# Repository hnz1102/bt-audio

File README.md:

# bt-audio

A Bluetooth A2DP sink for the original ESP32, written in Rust. It receives
audio from a phone or PC over Bluetooth Classic and plays it through two
TAS5754M class-D amplifiers (main L/R and woofer) fed over I2S. The volume of
each amplifier is set with a potentiometer.

The diagram also shows the planned FPGA DSP stage (crossover and filters)
between the ESP32 and the amplifiers. Until it exists, the ESP32 is wired
straight to both amplifiers.

## How it works

```
Bluetooth (A2DP/SBC) -> Bluedroid decoder -> bounded channel -> I2S writer thread -> 2x TAS5754M
                                                       volume knobs (ADC) -> I2C ---^
```

- The ESP32 advertises itself as `ESP32-Speaker` and accepts pairing
  automatically (SSP numeric comparison, with a legacy PIN of `1234` as
  fallback).
- Several devices can be paired; Bluedroid keeps the bonds in NVS. A new
  device can pair only while the speaker is discoverable: 3 min after
  "Pairing mode" in the web UI, and always while no device is paired (being
  discoverable takes radio time from the audio stream). Paired devices can connect whenever no other device is
  connected.
- At boot the speaker connects to the paired device that connected last; if
  that one is not reachable it tries the next most recent, and so on (up to
  8 devices). The order and the device names are kept in NVS (`src/bt.rs`).
- The Bluedroid stack decodes SBC and hands 16-bit stereo PCM to a callback
  running on the Bluetooth task. The callback copies each packet into a
  jitter buffer (at most 32 KB, ~185 ms) and drops it if the buffer is full
  or the free heap would fall below 12 KB, so a slow I2S write never stalls
  the Bluetooth stack. The drops are logged every minute by reason (buffer
  full / heap short, with the lowest free heap at a heap-short drop).
- Playback starts once 80 ms of audio is buffered, and buffers again after
  the stream paused long enough to run dry. Some sources (Windows PCs) pause
  and then send a burst; the buffer rides that out. The I2S DMA holds another
  ~43 ms. The `i2s-writer` thread runs on CPU1 at priority 15, away from the
  Bluetooth and WiFi tasks on CPU0. The buffer keeps 16-bit PCM, half the memory of the 32-bit DMA
  slots. The minute log reports underruns and rebuffers during playback, and
  after a drop or underrun also the buffer level, its peak and the free heap.
- A separate `i2s-writer` thread applies a software gain, then writes to the
  I2S channel.
- The I2S sample rate follows the rate negotiated by the source (16, 32,
  44.1 or 48 kHz).
- The I2S master outputs MCLK, BCK and WS. The APLL is the clock source, so
  the clocks are exact and low-jitter; if it cannot produce a rate the driver
  falls back to the 160 MHz PLL and logs a warning. MCLK is set to 256 x fs,
  but the original ESP32 puts the I2S module clock on GPIO0, so the pin
  carries 512 x fs (22.58 MHz at 44.1 kHz), which the TAS5754M accepts. GPIO0
  runs at the strongest drive, because the BOOT switch and the auto-reset
  transistor on it round a weaker edge into a triangle.
- The 2.1ch crossover runs on the ESP32: 4th-order Linkwitz-Riley, 150 Hz by
  default, set with `crossover_hz` (50-300 Hz) in the web UI. L/R are high-passed for the main
  amplifier; the mono sum (L+R)/2 is low-passed for the woofer. The woofer path also has
  a subsonic high-pass (4th order, 30 Hz by default) against cone buzz, set
  with `subsonic_hz` in the web UI (applies at once, 0 = off), and a bass EQ
  (peaking boost, Q 0.9; `bass_eq_hz` 30-150 Hz, default 60 Hz, `bass_eq_db`
  0-12 dB, default +6 dB) to make up for the small woofer's low-end roll-off.
  Keep the subsonic filter on when boosting.
- Both TAS5754M share one data line. I2S runs with 32-bit slots (BCK = 64 x fs);
  each slot holds the 16-bit main sample in its upper half and the 16-bit
  woofer sample in its lower half. Over I2C both amplifiers are set to I2S
  16-bit input; the woofer amplifier also gets an I2S shift of 16 SCLKs
  (P0-R41) so it reads the lower half. Both woofer channels carry the same
  mono signal. Their own DSP stays at its default.
- A peak limiter on each path (main L/R linked, woofer) turns loud peaks down
  instead of hard-clipping them; low-passing the mono sum can push bass peaks
  past full scale. How often it engaged is logged every 60 s.
- Volume ceiling from PVDD: the amplifiers' SPK_GAIN/FREQ divider (150 kΩ /
  750 kΩ, about 5.8 V) selects the 26 dBV gain, at which digital full scale
  would need a ~30 V output peak. The firmware measures PVDD through the
  AP33772S every 5 s and limits the volume register so full scale stays
  within 90 % of PVDD (about -4.5 dB at 20 V, -16.5 dB at 5 V). Change
  `AMP_GAIN_DBV` if the divider changes.
- If the woofer amplifier does not answer at boot, the crossover is off and the
  main amplifier plays the full range.
- After Bluetooth and the audio path are up, a `net` thread joins the WiFi
  network (see [WiFi, web UI and syslog](#wifi-web-ui-and-syslog)); the audio
  path never waits on it.
- At start-up, before the I2S and the amplifiers, the firmware talks to the
  AP33772S USB PD sink controller on the same I2C bus (address `0x52`): it
  reads the source's PDOs, enables the UVP/OVP/OCP protections, requests the
  highest voltage the source offers up to the `pd_max_mv` setting (24 V by default; a fixed
  PDO counts at its own voltage, a PPS/AVS PDO up to its maximum) and switches
  VOUT on once the negotiation succeeds. A PPS / AVS contract needs no
  keep-alive from the firmware: the AP33772S repeats the request itself. At boot the firmware waits up to
  5 s for the source to start USB PD; a failed negotiation is retried every
  minute. After start-up only the `controls` thread talks to the AP33772S. If no voltage is available or the
  request fails, VOUT stays off and an error is logged. The sequence follows the wrapper in
  `uv-controller`.
- An amplifier that does not answer on I2C at boot is treated as not fitted:
  it is left alone until the next reboot and the other one runs on its own
  (the web UI shows it as "not connected"). The I2C driver is installed from a
  task pinned to CPU1, so its interrupt runs away from the Bluetooth
  controller and WiFi on CPU0; on CPU0 it had tripped the interrupt watchdog.
- A `controls` thread reads the two knobs every 20 ms (ADC spikes dropped,
  smoothed, with hysteresis so a knob left alone never moves the volume). The
  volume is applied digitally on the ESP32, ramped sample by sample and
  dithered to 16 bits, so turning a knob does not click; the amplifier volume
  registers stay at the PVDD ceiling and are only used to mute. The main
  knob is the master volume for both amplifiers (0 dB down to -60 dB; fully
  counter-clockwise mutes both). The
  bass knob sets the woofer level against it: the lower half goes from -12 dB
  below the master up to the master level at mid rotation (fully
  counter-clockwise mutes the woofer); the upper half goes from the master
  level up to the woofer's full output at the top, whatever the master is, so
  the woofer can play at full with the main speakers quiet. Full output is the
  PVDD ceiling plus up to +6 dB of digital boost, with the woofer limiter
  holding the peaks. A muted knob unmutes only once it is clearly past the
  mute point, so noise near the bottom of the rotation cannot switch the
  sound on and off. The thread also watches `SPK_FAULT` and clears a latched
  fault by toggling `SPK_MUTE`.
- `SPK_MUTE` is low (muted) at boot and whenever no stream is running, and
  high while audio plays. The amplifiers ramp the volume, so there are no pops.

### The TAS5754M amplifier: closed loop and BTL

Japanese version: [docs/tas5754m_closed_loop_btl_ja.png](docs/tas5754m_closed_loop_btl_ja.png)

- **Closed loop.** Inside the TAS5754M the I2S data goes through the DSP
  (interpolation filter, digital volume) to a DAC, which produces the voltage
  the output should have. The PWM output of the H bridge is fed back (before
  the external LC filter) and compared with it; a loop filter integrates the
  difference and corrects the PWM duty cycle. The loop cancels PVDD ripple and
  changes (high PSRR) and the distortion of the output stage (MOSFET
  resistance, dead time).
- **Gain.** The gain is set by the feedback ratio only, selected with the
  `SPK_GAIN/FREQ` pin. This board's 150 kΩ / 750 kΩ divider selects
  26.4 dBV, at which digital full scale asks for about a 29.7 V output peak.
  The output cannot swing past about 90 % of PVDD (about 18 V at 20 V), so the
  firmware caps the volume from the measured PVDD (-4.5 dB at 20 V).
- **BTL (bridge-tied load).** Each channel has two half bridges, `OUT+` and
  `OUT-`, driving the two speaker terminals in opposite phase. The voltage
  across the speaker swings ±PVDD: twice the voltage and four times the
  power of a single-ended output, with no DC on the speaker and so no
  coupling capacitor. Neither speaker terminal may be connected to GND.
- **1SPW modulation.** In the TAS5754M mostly one side switches at a time
  (`OUT+` on positive half-waves, `OUT-` on negative ones) and at idle both
  sides only make narrow pulses, so the idle current is low; the TAS5756M's
  BD modulation has slightly lower distortion instead. The waveforms in the
  diagram are simplified.

The Rust side lives in [src/main.rs](src/main.rs). A small C component,
[components/bt_shim](components/bt_shim), wraps the Bluetooth controller
start-up, the I2S driver, the I2C bus and the ADC, whose configuration macros
and structs are awkward to use from Rust.

## Hardware

- An original ESP32 (classic Bluetooth is not available on the S2, S3, C3 and
  later chips).
- Two TAS5754M amplifiers wired as in Figure 83 of the datasheet (2.2 dual
  stereo BTL schematic, [tas5754m.pdf](tas5754m.pdf)): U400 drives the main
  L/R speakers, U401 the woofer. Supplies: PVDD 5-24 V for the amplifiers and
  3.3 V for the logic, shared with the ESP32.
- An AP33772S USB PD sink controller board on the I2C bus (SDA/SCL below,
  address `0x52`); its VOUT is the PVDD supply, which the TAS5754M allows up
  to 26.4 V.
- Two 10 kΩ B-taper (linear) potentiometers for the main and woofer volume.
  The firmware maps the rotation to the volume in dB evenly. For A-taper
  (audio) pots set `POT_TAPER_MID` to 0.15 (15 % at half rotation) and the
  firmware undoes the A curve; the default 0.5 is for a linear B pot.
- 16 MB flash (the partition table and `sdkconfig.defaults` assume it; adjust
  `CONFIG_ESPTOOLPY_FLASHSIZE_*` for other sizes).

### Wiring

| Signal | ESP32 GPIO | TAS5754M pin (both amplifiers) |
|--------|-----------|-------------------------------|
| BCK | 26 | SCLK (23) |
| WS / LRCK | 25 | LRCK/FS (25) |
| DATA (DOUT) | 22 | SDIN (24) |
| MCLK | 0 | MCLK (22) |
| SDA | 21 | SDA (16), 4.7 kΩ pull-up to 3.3 V |
| SCL | 18 | SCL (17), 4.7 kΩ pull-up to 3.3 V |
| Mute | 13 | SPK_MUTE (27), 100 kΩ pull-down to GND |
| Fault | 34 | SPK_FAULT (40), 10 kΩ pull-up to 3.3 V |
| Main volume | 33 (ADC1) | wiper of the main potentiometer |
| Woofer volume | 35 (ADC1) | wiper of the woofer potentiometer |

The pins are constants at the top of [src/main.rs](src/main.rs). Details:

- **I2C bus:** it runs at 100 kHz (the speed used by `uv-controller` for the
  AP33772S). The AP33772S (`0x52`) and the amplifiers (`0x4C`, `0x4D`) share it.
- **I2C addresses:** strap `ADR0`/`ADR1` so that U400 (main) is `0x4C`
  (`ADR0` = GND, `ADR1` = GND) and U401 (woofer) is `0x4D` (`ADR0` = 3.3 V,
  `ADR1` = GND).
- **MCLK on GPIO0:** the ESP32 can output MCLK only on GPIO0, 1 or 3. GPIO0 is
  a boot strapping pin: power the amplifiers' DVDD from the same 3.3 V rail as
  the ESP32 so that their MCLK input never holds GPIO0 low at boot.
- **Potentiometers:** connect one end to 3.3 V and the other through a 1 kΩ
  resistor to GND, the wiper to the GPIO and a 0.1 µF capacitor from the
  wiper to GND. Both pins are on ADC1, which works with Bluetooth active. The
  resistor lifts the counter-clockwise stop to about 0.3 V, above the ESP32
  ADC's dead zone (below ~0.15 V), so the knob has no slack at that end. The
  firmware learns the stop reading (the lowest reading seen, kept in NVS as
  `knob_floor33` / `knob_floor35`) and mutes within 20 counts of it; until
  the knob has been turned to its stop once, it mutes below 520. A factory
  reset erases the learned value.
- **Clock signals:** a 33 Ω series resistor near the ESP32 on each of BCK, WS,
  MCLK and DOUT reduces ringing and EMI.
- Leave the amplifiers' `GPIO0/1/2` unconnected. The output filters, PVDD
  network and the `SPK_GAIN/FREQ` divider follow the datasheet schematic.

> **Keep GPIO6-11 clear.** These pins connect the module to its internal SPI
> flash. If they are wired to anything external, noise can corrupt
> instruction fetches and cause random `IllegalInstruction` panics, typically
> when Bluetooth audio starts.

## WiFi, web UI and syslog

The settings are stored in NVS (namespace `btaudio_cfg`) and edited in a web
UI. The WiFi, WPS and syslog code follows the one in eew-display.

**WiFi and WPS.** With no SSID stored and WPS enabled (the default), the
firmware starts a WPS push-button handshake at boot: press the WPS button on
the router within 120 s. The received SSID and passphrase are saved to NVS,
so the next boot connects directly. A station that is not connected retries
every 30 s. The WiFi modem sleeps between beacons (`WIFI_PS_MIN_MODEM`) to
leave airtime for the Bluetooth stream. WPS can also be started later from the
web UI ("Start WPS now"). There is no access-point mode.

**Web UI.** Once connected, open `http://<host name or IP address>/` (the IP
address is in the log: `WiFi up, IP address ...`). Log in with the default
user `admin` and password `btpass` (set in [cfg.toml](cfg.toml)), and change
them under "Account". The server speaks plain HTTP, so use it on a trusted
network only.

The page has these sections, from the top (the screenshot shows sample
values):

- **Status**, refreshed every 5 s: local time, uptime, WiFi address / SSID /
  RSSI, Bluetooth state (not connected / connected / playing), sample rate,
  the volume of each amplifier, amplifier fault, the measured USB PD voltage
  and current with the requested voltage, free heap (and its minimum since
  boot), firmware version.
- **Bluetooth devices**: the paired devices, most recently connected first,
  with name, address, `connected` and `last` (tried first at boot).
  "Remove" forgets a device (it is disconnected first). "Pairing mode
  (3 min)" makes the speaker discoverable so a new device can pair; a
  connected device is disconnected for it, since the speaker cannot be found
  while connected. The line above the button shows whether the speaker is
  discoverable and for how long.
- **Audio**: software gain, crossover frequency, woofer subsonic high-pass,
  bass EQ boost and frequency. The sliders apply while moving
  (`/api/live`) and are kept after a reboot only when saved. Also the volume
  knob range (applied at once), the Bluetooth name and the USB PD maximum
  voltage (both after a reboot).
- **WiFi**: SSID, password, WPS at boot when no SSID is set (after a reboot);
  "Start WPS now" starts a WPS push-button handshake at once.
- **Network**: host name (DHCP and syslog), DHCP or static IP address,
  subnet mask, gateway, DNS, four NTP servers (after a reboot), and the time
  zone as a POSIX TZ string (default `JST-9`, applied at once).
- **Syslog**: forwarding on/off, server `host[:port]` (UDP, port 514 by
  default) and application name (applied at once).
- **Account**: web UI user and password (after a reboot).

"Save" stores every section. "Reboot" restarts the ESP32; "Factory reset"
erases the settings and the learned knob stops (not the paired devices) and
reboots. The passwords are never sent back to the browser; leave a password
field empty to keep it.

<br clear="right">

**Syslog.** When enabled, every log record is also sent to the syslog server
as an RFC 5424 message over UDP (facility user, app name `bt-audio`, host name
from the settings). The timestamp is the local time (from SNTP and the time-zone
setting) with its UTC offset, e.g. `2026-11-17T23:53:01+09:00`, and is `-`
until the clock has been set. The log is always written to the serial console as well.
Messages are queued and sent by a separate thread, so logging never blocks the
Bluetooth tasks; they are dropped if the queue is full.

**Memory.** WiFi and the web server share the heap with Bluetooth (about 129 KB
free with Bluetooth alone). The WiFi buffers and sockets are reduced in
[sdkconfig.defaults](sdkconfig.defaults) and A-MPDU is disabled. After the
network is up the log prints `heap free ... bytes, minimum ...`, and the web UI
shows the same: check the minimum while a stream plays and the UI is in use.

## Building and flashing

### 1. Set up the environment

On Ubuntu / Debian (including WSL2), run the setup script once:

```sh
bash setup_env.sh
```

It installs the system packages, Rust (rustup), `ldproxy`, `espup` and
`cargo-espflash`, the Xtensa toolchain for the ESP32 (`espup install
--targets esp32`), and adds your user to the `dialout` group for serial port
access (log out and back in afterwards).

In every new terminal, load the Rust and ESP environments before building:

```sh
source "$HOME/.cargo/env"
source "$HOME/export-esp.sh"
```

ESP-IDF v5.2.2 is downloaded and built automatically by `esp-idf-sys` on the
first build, which takes a while.

### 2. Build and flash

```sh
cargo build --release
cargo espflash flash --release --monitor --port /dev/ttyUSB0
```

The target, ESP-IDF version and `build-std` are configured in
[.cargo/config.toml](.cargo/config.toml). The partition table is
[partitions.csv](partitions.csv): a single 3 MB factory app, because the
default 1 MB partition is too small with Bluedroid.

Press `Ctrl+R` in the monitor to reset the chip. This works when the
USB-serial chip's DTR/RTS lines are wired to EN and GPIO0, as on most
development boards.

## Configuration

Constants in [src/main.rs](src/main.rs):

| Constant | Default | Meaning |
|----------|---------|---------|
| `DEFAULT_SAMPLE_RATE` | `44_100` | I2S rate before the source negotiates one |
| `GAIN_Q8` | `256` | Initial software gain in Q8 fixed point (256 = 1.0x); the setting from the web UI replaces it |
| `PREFILL_MS` | `80` | Audio buffered before playback starts or resumes after running dry |
| `QUEUE_MAX_BYTES` | 32 KB | Most PCM buffered between the Bluetooth task and the I2S writer (~185 ms at 44.1 kHz) |
| `HEAP_FLOOR` | 12 KB | A packet is dropped rather than buffered when the free heap would fall below this |
| `PIN_BCK`, `PIN_WS`, `PIN_DOUT`, `PIN_MCLK` | 26, 25, 22, 0 | I2S pins |
| `PIN_SDA`, `PIN_SCL` | 21, 18 | I2C pins |
| `AMP_MAIN`, `AMP_WOOFER` | `0x4C`, `0x4D` | Amplifier I2C addresses (7-bit) |
| `PIN_MUTE`, `PIN_FAULT` | 13, 34 | `SPK_MUTE` output, `SPK_FAULT` input |
| `PD_LOG_INTERVAL` | 60 s | How often the measured USB PD voltage and current are logged |
| `PD_POLL_INTERVAL` | 5 s | USB PD polling: measures the output for the log and the web UI; a failed negotiation is retried every minute |
| `CURRENT_SAMPLE_INTERVAL` | 200 ms | USB PD output current sampling; the log line every 60 s shows `PD <mV>, <avg> mA avg / <max> mA max` (24 mA resolution) |
| `PIN_VOL_MAIN`, `PIN_VOL_WOOFER` | 33, 35 | Master volume and bass knob ADC pins |
| `BASS_RANGE_STEPS` | `24` | Bass knob range in 0.5 dB steps either side of 0 dB (24 = +-12 dB) |
| `VOL_RANGE_STEPS` | `120` | Initial knob range in 0.5 dB steps (120 = 0 to -60 dB); the `vol_range_db` setting replaces it |

Build-time settings are in [sdkconfig.defaults](sdkconfig.defaults): classic
Bluetooth only (BR/EDR), Bluedroid with A2DP and SSP, a custom partition
table, and 16 MB flash.

## Troubleshooting

- **Random `IllegalInstruction` panics or garbled backtraces**: check the
  flash pins (GPIO6-11) and keep wiring away from the antenna. Lowering the
  flash clock with `CONFIG_ESPTOOLPY_FLASHFREQ_20M=y` (and flashing with
  `-f 20mhz`) can help as a diagnostic, but removing the noise source is the
  real fix.
- **Distorted sound**: lower the software gain (above 256 clips) and the volume knobs,
  and check the source volume, the PVDD supply and the speaker wiring.
- **No sound but connected**: check the log for `audio state 1` and for
  `amp 0x4c ready` / `amp 0x4d ready`. A failed I2C write is logged as
  `amp ... init failed`: check SDA/SCL, the pull-ups and the `ADR0`/`ADR1`
  straps. Verify that `SPK_MUTE` is high while playing.
- **No PD output**: the log lists the source's PDOs (`PDO n: ... mV`) and then
  `USB PD output on` or `USB PD output not enabled: ...`. The log also shows
  `selected ... mV`, the highest voltage offered up to the `pd_max_mv` setting.
- **Clock errors on the amplifiers**: the `clock status` value in the
  `amp ... ready` log line is `P0-R94` of the TAS5754M; `0x00` means MCLK, SCLK
  and the sampling rate are valid. Check the MCLK wiring if it is not.
- **`SPK_FAULT` messages**: the amplifier reports over-current, over-temperature,
  under/over-voltage or a DC fault; check the speaker wiring and PVDD.

## Limitations

- SBC only; no AAC or other codecs.
- No AVRCP (volume and playback control from the sink side).
- One connection at a time; the device stops being discoverable while
  connected. No reconnect after a link loss (only at boot).
- The crossover and filters run on the ESP32 for now; the planned FPGA stage
  between the ESP32 and the amplifiers would take them over.

## License

**Software** (firmware, [src/](src/), [components/](components/)): MIT License.
Copyright (c) 2026 Hiroshi Nakajima. The license is declared in the header of
[src/main.rs](src/main.rs) (`SPDX-License-Identifier: MIT`) and in
[Cargo.toml](Cargo.toml) (`license = "MIT"`).

**Hardware** (schematic, PCB layout, BOM and production files in [hw/](hw/)):
[Creative Commons Attribution-ShareAlike 4.0 International](https://creativecommons.org/licenses/by-sa/4.0/)
(CC BY-SA 4.0). Copyright (c) 2026 Hiroshi Nakajima. You may copy, modify,
manufacture and sell boards made from these files, provided you credit the
author and release modified design files under the same license.

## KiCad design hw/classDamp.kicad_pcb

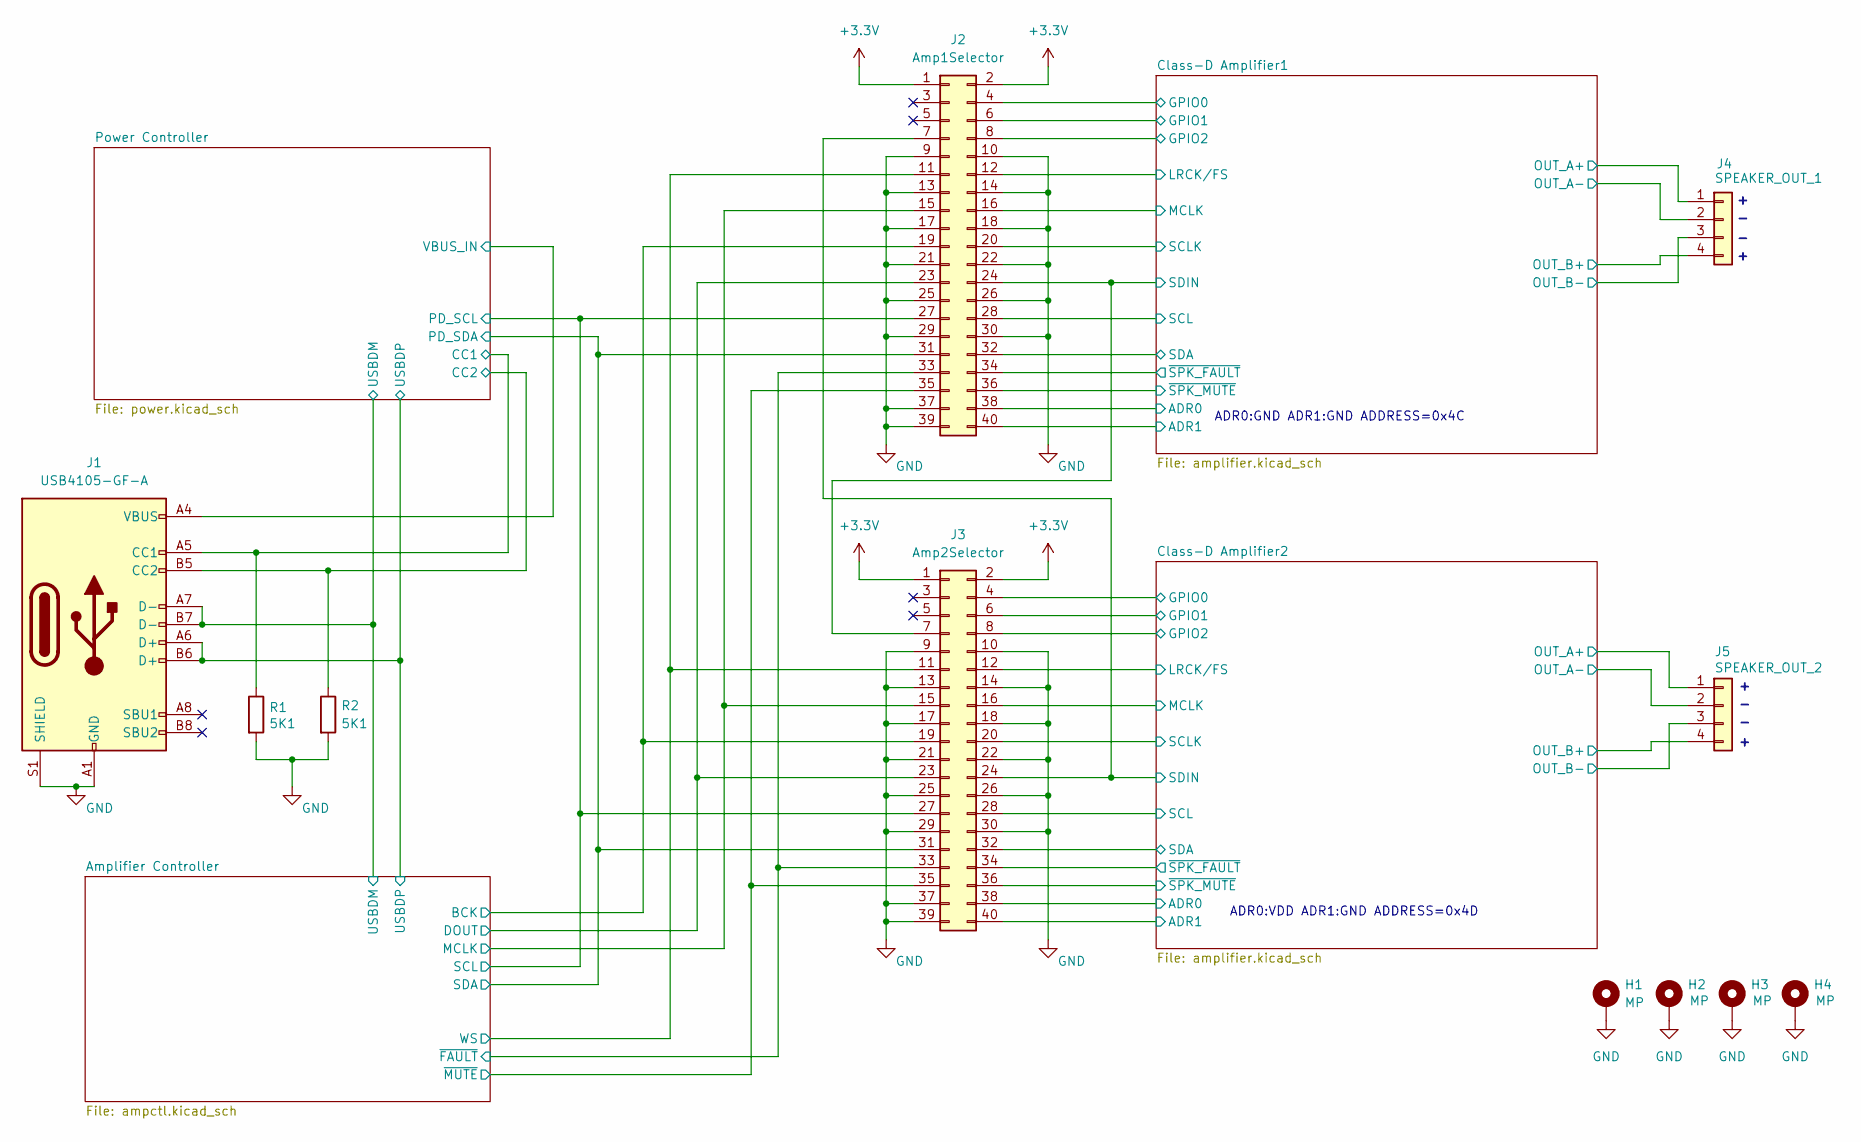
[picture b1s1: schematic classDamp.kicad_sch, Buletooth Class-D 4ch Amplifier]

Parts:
H1, H2, H3, H4: MP; MountingHole_3.2mm_M3_Pad_Via
J1: USB4105-GF-A; USB_C_5077CR-16-SMC2-BK-TR; digikey 2073-USB4105-GF-ACT-ND
J2: Amp1Selector; PinHeader_2x20_P2.54mm_Vertical; digikey 100080
J3: Amp2Selector; PinHeader_2x20_P2.54mm_Vertical; digikey 100080
J4: SPEAKER_OUT_1; JST_VH_B4P-VH_1x04_P3.96mm_Vertical; digikey 112817
J5: SPEAKER_OUT_2; JST_VH_B4P-VH_1x04_P3.96mm_Vertical; digikey 112817
R1, R2: 5K1; R_0603_1608Metric; digikey 311-5.10KHRCT-ND

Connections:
+3.3V: J2.1, J2.2, J3.1, J3.2; also elsewhere on the board
/Amplifier Controller/BCK: J2.19, J3.19; also elsewhere on the board
/Amplifier Controller/DOUT: J2.23, J3.23; also elsewhere on the board
/Amplifier Controller/MCLK: J2.15, J3.15; also elsewhere on the board
/Amplifier Controller/SCL: J2.27, J3.27; also elsewhere on the board
/Amplifier Controller/SDA: J2.31, J3.31; also elsewhere on the board
/Amplifier Controller/USBDM: J1.A7 (D-), J1.B7 (D-); also elsewhere on the board
/Amplifier Controller/USBDP: J1.A6 (D+), J1.B6 (D+); also elsewhere on the board
/Amplifier Controller/WS: J2.11, J3.11; also elsewhere on the board
/Amplifier Controller/~FAULT: J2.33, J3.33; also elsewhere on the board
/Amplifier Controller/~MUTE: J2.35, J3.35; also elsewhere on the board
/Class-D Amplifier1/ADR0: J2.38; also elsewhere on the board
/Class-D Amplifier1/ADR1: J2.40; also elsewhere on the board
/Class-D Amplifier1/GPIO0: J2.4; also elsewhere on the board
/Class-D Amplifier1/GPIO1: J2.6; also elsewhere on the board
/Class-D Amplifier1/GPIO2: J2.8; also elsewhere on the board
/Class-D Amplifier1/LRCK/FS: J2.12; also elsewhere on the board
/Class-D Amplifier1/MCLK: J2.16; also elsewhere on the board
/Class-D Amplifier1/OUT_A+: J4.1; also elsewhere on the board
/Class-D Amplifier1/OUT_A-: J4.2; also elsewhere on the board
/Class-D Amplifier1/OUT_B+: J4.4; also elsewhere on the board
/Class-D Amplifier1/OUT_B-: J4.3; also elsewhere on the board
/Class-D Amplifier1/SCL: J2.28; also elsewhere on the board
/Class-D Amplifier1/SCLK: J2.20; also elsewhere on the board
/Class-D Amplifier1/SDA: J2.32; also elsewhere on the board
/Class-D Amplifier1/SDIN: J2.24, J3.7; also elsewhere on the board
/Class-D Amplifier1/~SPK_FAULT: J2.34; also elsewhere on the board
/Class-D Amplifier1/~SPK_MUTE: J2.36; also elsewhere on the board
/Class-D Amplifier2/ADR0: J3.38; also elsewhere on the board
/Class-D Amplifier2/ADR1: J3.40; also elsewhere on the board
/Class-D Amplifier2/GPIO0: J3.4; also elsewhere on the board
/Class-D Amplifier2/GPIO1: J3.6; also elsewhere on the board
/Class-D Amplifier2/GPIO2: J3.8; also elsewhere on the board
/Class-D Amplifier2/LRCK/FS: J3.12; also elsewhere on the board
/Class-D Amplifier2/MCLK: J3.16; also elsewhere on the board
/Class-D Amplifier2/OUT_A+: J5.1; also elsewhere on the board
/Class-D Amplifier2/OUT_A-: J5.2; also elsewhere on the board
/Class-D Amplifier2/OUT_B+: J5.4; also elsewhere on the board
/Class-D Amplifier2/OUT_B-: J5.3; also elsewhere on the board
/Class-D Amplifier2/SCL: J3.28; also elsewhere on the board
/Class-D Amplifier2/SCLK: J3.20; also elsewhere on the board
/Class-D Amplifier2/SDA: J3.32; also elsewhere on the board
/Class-D Amplifier2/SDIN: J2.7, J3.24; also elsewhere on the board
/Class-D Amplifier2/~SPK_FAULT: J3.34; also elsewhere on the board
/Class-D Amplifier2/~SPK_MUTE: J3.36; also elsewhere on the board
/Power Controller/CC1: J1.A5 (CC1), R1.1; also elsewhere on the board
/Power Controller/CC2: J1.B5 (CC2), R2.1; also elsewhere on the board
/Power Controller/VBUS_IN: J1.A4 (VBUS), J1.A9 (VBUS), J1.B4 (VBUS), J1.B9 (VBUS); also elsewhere on the board
GND: H1.1 (1_1), H2.1 (1_1), H3.1 (1_1), H4.1 (1_1), J1.A1 (GND), J1.A12 (GND), J1.B1 (GND), J1.B12 (GND), J1.S1 (SHIELD), J2.9, J2.10, J2.13, J2.14, J2.17, J2.18, J2.21, J2.22, J2.25, J2.26, J2.29, J2.30, J2.37, J2.39, J3.9, J3.10, J3.13, J3.14, J3.17, J3.18, J3.21, J3.22, J3.25, J3.26, J3.29, J3.30, J3.37, J3.39, R1.2, R2.2; also elsewhere on the board

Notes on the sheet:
ADR0:GND ADR1:GND ADDRESS=0x4C
ADR0:VDD ADR1:GND ADDRESS=0x4D

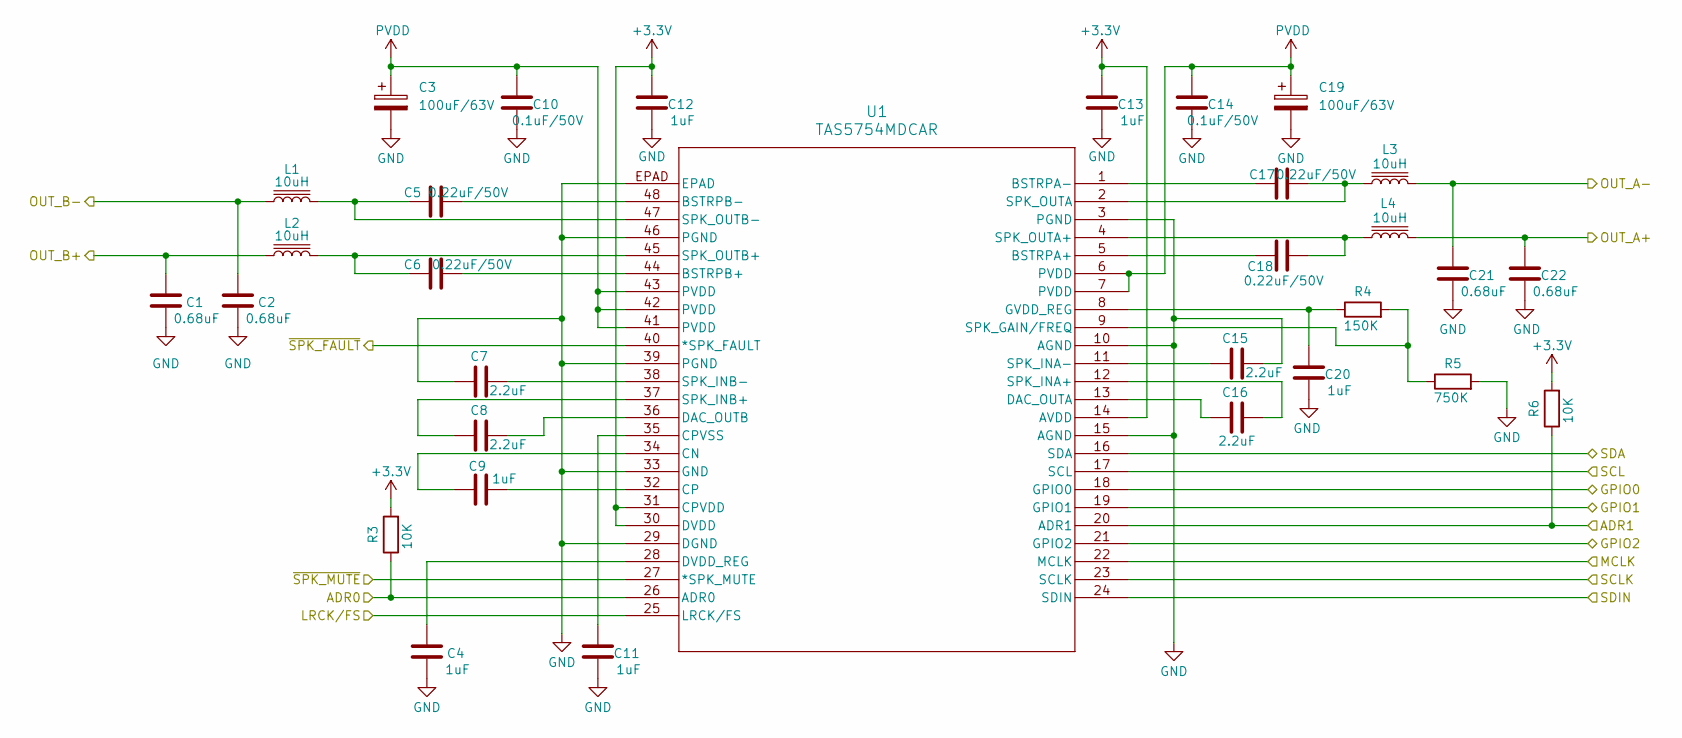
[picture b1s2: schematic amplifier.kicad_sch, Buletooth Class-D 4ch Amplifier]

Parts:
C1, C2, C21, C22: 0.68uF; C_1206_3216Metric; digikey 445-4013-1-ND
C3, C19: 100uF/63V; CP_Elec_10x12.5; digikey 63SGV100M10x10.5/112940
C4, C9, C11, C12, C13, C20: 1uF; C_0805_2012Metric; digikey 1276-1026-1-ND
C5, C6, C17, C18: 0.22uF/50V; C_1206_3216Metric; digikey 115773
C7, C8, C15, C16: 2.2uF; C_0603_1608Metric; digikey 1276-1040-1-ND
C10, C14: 0.1uF/50V; C_0603_1608Metric; digikey 311-1344-1-ND
L1, L2, L3, L4: 10uH; Inductor_7G14C; digikey 115257
R3, R6: 10K; R_0603_1608Metric; digikey 311-10.0KHRCT-ND
R4: 150K; R_0603_1608Metric; digikey 13-RC0603FR-13150KLCT-ND
R5: 750K; R_0603_1608Metric; digikey 311-750KHRCT-ND
U1: TAS5754MDCAR; DCA48_6P4X3P6_TEX; digikey 296-40564-1-ND

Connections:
+3.3V: C12.1, C13.1, R3.2, R6.2, U1.14 (AVDD), U1.30 (DVDD), U1.31 (CPVDD); also elsewhere on the board
/Class-D Amplifier1/ADR0: R3.1, U1.26 (ADR0); also elsewhere on the board
/Class-D Amplifier1/ADR1: R6.1, U1.20 (ADR1); also elsewhere on the board
/Class-D Amplifier1/GPIO0: U1.18 (GPIO0); also elsewhere on the board
/Class-D Amplifier1/GPIO1: U1.19 (GPIO1); also elsewhere on the board
/Class-D Amplifier1/GPIO2: U1.21 (GPIO2); also elsewhere on the board
/Class-D Amplifier1/LRCK/FS: U1.25 (LRCK/FS); also elsewhere on the board
/Class-D Amplifier1/MCLK: U1.22 (MCLK); also elsewhere on the board
/Class-D Amplifier1/OUT_A+: C22.1, L4.2; also elsewhere on the board
/Class-D Amplifier1/OUT_A-: C21.1, L3.2; also elsewhere on the board
/Class-D Amplifier1/OUT_B+: C1.1, L2.2; also elsewhere on the board
/Class-D Amplifier1/OUT_B-: C2.1, L1.2; also elsewhere on the board
/Class-D Amplifier1/SCL: U1.17 (SCL); also elsewhere on the board
/Class-D Amplifier1/SCLK: U1.23 (SCLK); also elsewhere on the board
/Class-D Amplifier1/SDA: U1.16 (SDA); also elsewhere on the board
/Class-D Amplifier1/SDIN: U1.24 (SDIN); also elsewhere on the board
/Class-D Amplifier1/~SPK_FAULT: U1.40 (*SPK_FAULT); also elsewhere on the board
/Class-D Amplifier1/~SPK_MUTE: U1.27 (*SPK_MUTE); also elsewhere on the board
GND: C1.2, C2.2, C3.2, C4.2, C7.1, C10.2, C11.2, C12.2, C13.2, C14.2, C15.2, C19.2, C20.2, C21.2, C22.2, R5.2, U1.3 (PGND), U1.10 (AGND), U1.15 (AGND), U1.29 (DGND), U1.33 (GND), U1.39 (PGND), U1.46 (PGND), U1.EPAD; also elsewhere on the board
unnamed: C18.1, U1.5 (BSTRPA+)
unnamed: C17.1, U1.1 (BSTRPA-)
unnamed: C6.2, U1.44 (BSTRPB+)
unnamed: C5.2, U1.48 (BSTRPB-)
unnamed: C9.1, U1.34 (CN)
unnamed: C9.2, U1.32 (CP)
unnamed: C11.1, U1.35 (CPVSS)
unnamed: C16.1, U1.13 (DAC_OUTA)
unnamed: C8.2, U1.36 (DAC_OUTB)
unnamed: C4.1, U1.28 (DVDD_REG)
unnamed: C20.1, R4.1, U1.8 (GVDD_REG)
unnamed: R4.2, R5.1, U1.9 (SPK_GAIN/FREQ)
unnamed: C16.2, U1.12 (SPK_INA+)
unnamed: C15.1, U1.11 (SPK_INA-)
unnamed: C8.1, U1.37 (SPK_INB+)
unnamed: C7.2, U1.38 (SPK_INB-)
unnamed: C17.2, L3.1, U1.2 (SPK_OUTA)
unnamed: C18.2, L4.1, U1.4 (SPK_OUTA+)
unnamed: C6.1, L2.1, U1.45 (SPK_OUTB+)
unnamed: C5.1, L1.1, U1.47 (SPK_OUTB-)
PVDD: C3.1, C10.1, C14.1, C19.1, U1.6 (PVDD), U1.7 (PVDD), U1.41 (PVDD), U1.42 (PVDD), U1.43 (PVDD); also elsewhere on the board

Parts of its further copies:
C23, C24, C43, C44: 0.68uF; C_1206_3216Metric; digikey 445-4013-1-ND
C25, C41: 100uF/63V; CP_Elec_10x12.5; digikey 63SGV100M10x10.5/112940
C26, C31, C33, C34, C35, C42: 1uF; C_0805_2012Metric; digikey 1276-1026-1-ND
C27, C28, C39, C40: 0.22uF/50V; C_1206_3216Metric; digikey 115773
C29, C30, C37, C38: 2.2uF; C_0603_1608Metric; digikey 1276-1040-1-ND
C32, C36: 0.1uF/50V; C_0603_1608Metric; digikey 311-1344-1-ND
L5, L6, L7, L8: 10uH; Inductor_7G14C; digikey 115257
R7, R10: 10K; R_0603_1608Metric; digikey 311-10.0KHRCT-ND
R8: 150K; R_0603_1608Metric; digikey 13-RC0603FR-13150KLCT-ND
R9: 750K; R_0603_1608Metric; digikey 311-750KHRCT-ND
U2: TAS5754MDCAR; DCA48_6P4X3P6_TEX; digikey 296-40564-1-ND

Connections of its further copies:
+3.3V: C34.1, C35.1, R7.2, R10.2, U2.14 (AVDD), U2.30 (DVDD), U2.31 (CPVDD); also elsewhere on the board
/Class-D Amplifier2/ADR0: R7.1, U2.26 (ADR0); also elsewhere on the board
/Class-D Amplifier2/ADR1: R10.1, U2.20 (ADR1); also elsewhere on the board
/Class-D Amplifier2/GPIO0: U2.18 (GPIO0); also elsewhere on the board
/Class-D Amplifier2/GPIO1: U2.19 (GPIO1); also elsewhere on the board
/Class-D Amplifier2/GPIO2: U2.21 (GPIO2); also elsewhere on the board
/Class-D Amplifier2/LRCK/FS: U2.25 (LRCK/FS); also elsewhere on the board
/Class-D Amplifier2/MCLK: U2.22 (MCLK); also elsewhere on the board
/Class-D Amplifier2/OUT_A+: C44.1, L8.2; also elsewhere on the board
/Class-D Amplifier2/OUT_A-: C43.1, L7.2; also elsewhere on the board
/Class-D Amplifier2/OUT_B+: C23.1, L6.2; also elsewhere on the board
/Class-D Amplifier2/OUT_B-: C24.1, L5.2; also elsewhere on the board
/Class-D Amplifier2/SCL: U2.17 (SCL); also elsewhere on the board
/Class-D Amplifier2/SCLK: U2.23 (SCLK); also elsewhere on the board
/Class-D Amplifier2/SDA: U2.16 (SDA); also elsewhere on the board
/Class-D Amplifier2/SDIN: U2.24 (SDIN); also elsewhere on the board
/Class-D Amplifier2/~SPK_FAULT: U2.40 (*SPK_FAULT); also elsewhere on the board
/Class-D Amplifier2/~SPK_MUTE: U2.27 (*SPK_MUTE); also elsewhere on the board
GND: C23.2, C24.2, C25.2, C26.2, C29.1, C32.2, C33.2, C34.2, C35.2, C36.2, C37.2, C41.2, C42.2, C43.2, C44.2, R9.2, U2.3 (PGND), U2.10 (AGND), U2.15 (AGND), U2.29 (DGND), U2.33 (GND), U2.39 (PGND), U2.46 (PGND), U2.EPAD; also elsewhere on the board
unnamed: C40.1, U2.5 (BSTRPA+)
unnamed: C39.1, U2.1 (BSTRPA-)
unnamed: C28.2, U2.44 (BSTRPB+)
unnamed: C27.2, U2.48 (BSTRPB-)
unnamed: C31.1, U2.34 (CN)
unnamed: C31.2, U2.32 (CP)
unnamed: C33.1, U2.35 (CPVSS)
unnamed: C38.1, U2.13 (DAC_OUTA)
unnamed: C30.2, U2.36 (DAC_OUTB)
unnamed: C26.1, U2.28 (DVDD_REG)
unnamed: C42.1, R8.1, U2.8 (GVDD_REG)
unnamed: R8.2, R9.1, U2.9 (SPK_GAIN/FREQ)
unnamed: C38.2, U2.12 (SPK_INA+)
unnamed: C37.1, U2.11 (SPK_INA-)
unnamed: C30.1, U2.37 (SPK_INB+)
unnamed: C29.2, U2.38 (SPK_INB-)
unnamed: C39.2, L7.1, U2.2 (SPK_OUTA)
unnamed: C40.2, L8.1, U2.4 (SPK_OUTA+)
unnamed: C28.1, L6.1, U2.45 (SPK_OUTB+)
unnamed: C27.1, L5.1, U2.47 (SPK_OUTB-)
PVDD: C25.1, C32.1, C36.1, C41.1, U2.6 (PVDD), U2.7 (PVDD), U2.41 (PVDD), U2.42 (PVDD), U2.43 (PVDD); also elsewhere on the board

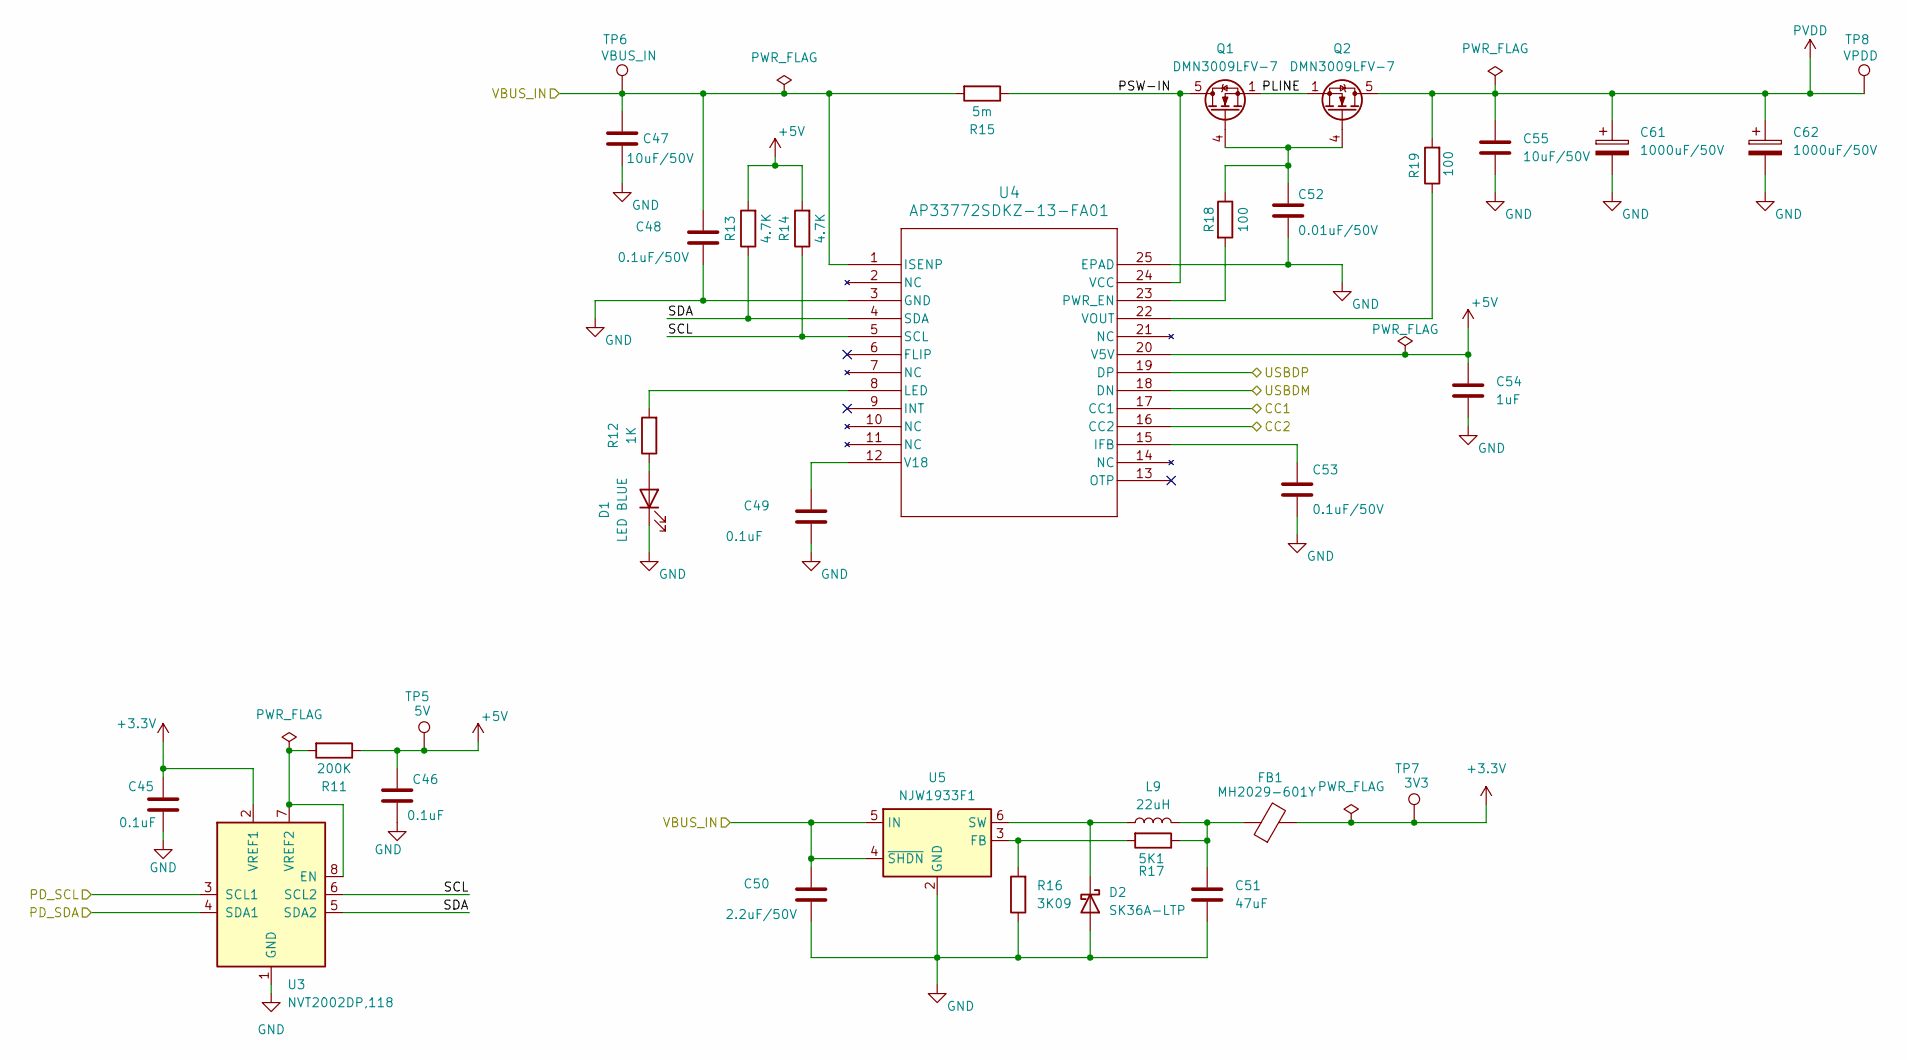
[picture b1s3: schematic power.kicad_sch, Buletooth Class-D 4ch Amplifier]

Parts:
C45, C46, C49: 0.1uF; C_0603_1608Metric; digikey 311-1343-1-ND
C47, C55: 10uF/50V; C_0805_2012Metric; digikey 490-GRM21BR61H106KE43KCT-ND
C48, C53: 0.1uF/50V; C_0603_1608Metric; digikey 311-1344-1-ND
C50: 2.2uF/50V; C_0603_1608Metric; digikey 587-4320-1-ND
C51: 47uF; C_0805_2012Metric; digikey 587-4280-1-ND
C52: 0.01uF/50V; C_0603_1608Metric; digikey 311-1085-1-ND
C54: 1uF; C_0805_2012Metric; digikey 1276-1026-1-ND
C61, C62: 1000uF/50V; CP_Radial_D16.0mm_P7.50mm; digikey 108442
D1: LED BLUE; LED_0603_1608Metric; digikey 3147-B1931NB--20C007614U1930CT-ND
D2: SK36A-LTP; D_SMA; digikey SK36A-LTPMSCT-ND
FB1: MH2029-601Y; L_0805_2012Metric; digikey MH2029-601YCT-ND
L9: 22uH; L_CHPH4D19FNP; digikey 308-1313-1-ND
Q1, Q2: DMN3009LFV-7; Diodes_PowerDI3333-8; digikey 31-DMN3009LFV-7CT-ND
R11: 200K; R_0603_1608Metric; digikey 311-200KHRCT-ND
R12: 1K; R_0603_1608Metric; digikey 311-1.00KHRCT-ND
R13, R14: 4.7K; R_0603_1608Metric; digikey 311-4.70KHRCT-ND
R15: 5m; R_2512_6332Metric_Pad1.40x3.35mm_HandSolder; digikey 4506-PEWF2512D5L00Q9CT-ND
R16: 3K09; R_0603_1608Metric; digikey 311-3.09KHRCT-ND
R17: 5K1; R_0603_1608Metric; digikey 311-5.10KHRCT-ND
R18, R19: 100; R_0603_1608Metric; digikey 311-100CRCT-ND
TP5: 5V; TestPoint_Pad_D1.0mm
TP6: VBUS_IN; TestPoint_Pad_D1.0mm
TP7: 3V3; TestPoint_Pad_D1.0mm
TP8: VPDD; TestPoint_Pad_D1.0mm
U3: NVT2002DP,118; TSSOP-8_3x3mm_P0.65mm; digikey 568-5121-1-ND
U4: AP33772SDKZ-13-FA01; W-QFN4040-24_Type_A1_DIO; digikey 31-AP33772SDKZ-13-FA01CT-ND
U5: NJW1933F1; SOT-23-6; digikey 2129-NJW1933F1-AT-TE2-ND

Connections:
+3.3V: C45.1, FB1.2, TP7.1 (1_1), U3.2 (VREF1); also elsewhere on the board
+5V: C46.1, C54.1, R11.1, R13.2, R14.2, TP5.1 (1_1), U4.20 (V5V)
/Amplifier Controller/SCL: U3.3 (SCL1); also elsewhere on the board
/Amplifier Controller/SDA: U3.4 (SDA1); also elsewhere on the board
/Amplifier Controller/USBDM: U4.18 (DN); also elsewhere on the board
/Amplifier Controller/USBDP: U4.19 (DP); also elsewhere on the board
/Power Controller/CC1: U4.17 (CC1); also elsewhere on the board
/Power Controller/CC2: U4.16 (CC2); also elsewhere on the board
/Power Controller/PLINE: Q1.1 (S), Q1.2 (S), Q1.3 (S), Q2.1 (S), Q2.2 (S), Q2.3 (S)
/Power Controller/PSW-IN: Q1.5 (D), R15.1, U4.24 (VCC)
/Power Controller/SCL: R14.1, U3.6 (SCL2), U4.5 (SCL)
/Power Controller/SDA: R13.1, U3.5 (SDA2), U4.4 (SDA)
/Power Controller/VBUS_IN: C47.1, C48.1, C50.1, R15.2, TP6.1 (1_1), U4.1 (ISENP), U5.4 (~SHDN), U5.5 (IN); also elsewhere on the board
GND: C45.2, C46.2, C47.2, C48.2, C49.2, C50.2, C51.2, C52.2, C53.2, C54.2, C55.2, C61.2, C62.2, D1.1 (K), D2.2 (A), R16.1, U3.1 (GND), U4.3 (GND), U4.25 (EPAD), U5.2 (GND); also elsewhere on the board
unnamed: C51.1, FB1.1, L9.2, R17.1
unnamed: D1.2 (A), R12.1
unnamed: D2.1 (K), L9.1, U5.6 (SW)
unnamed: C52.1, Q1.4 (G), Q2.4 (G), R18.1
unnamed: R11.2, U3.7 (VREF2), U3.8 (EN)
unnamed: C53.1, U4.15 (IFB)
unnamed: R12.2, U4.8 (LED)
unnamed: R18.2, U4.23 (PWR_EN)
unnamed: C49.1, U4.12 (V18)
unnamed: R19.1, U4.22 (VOUT)
unnamed: R16.2, R17.2, U5.3 (FB)
PVDD: C55.1, C61.1, C62.1, Q2.5 (D), R19.2, TP8.1 (1_1); also elsewhere on the board

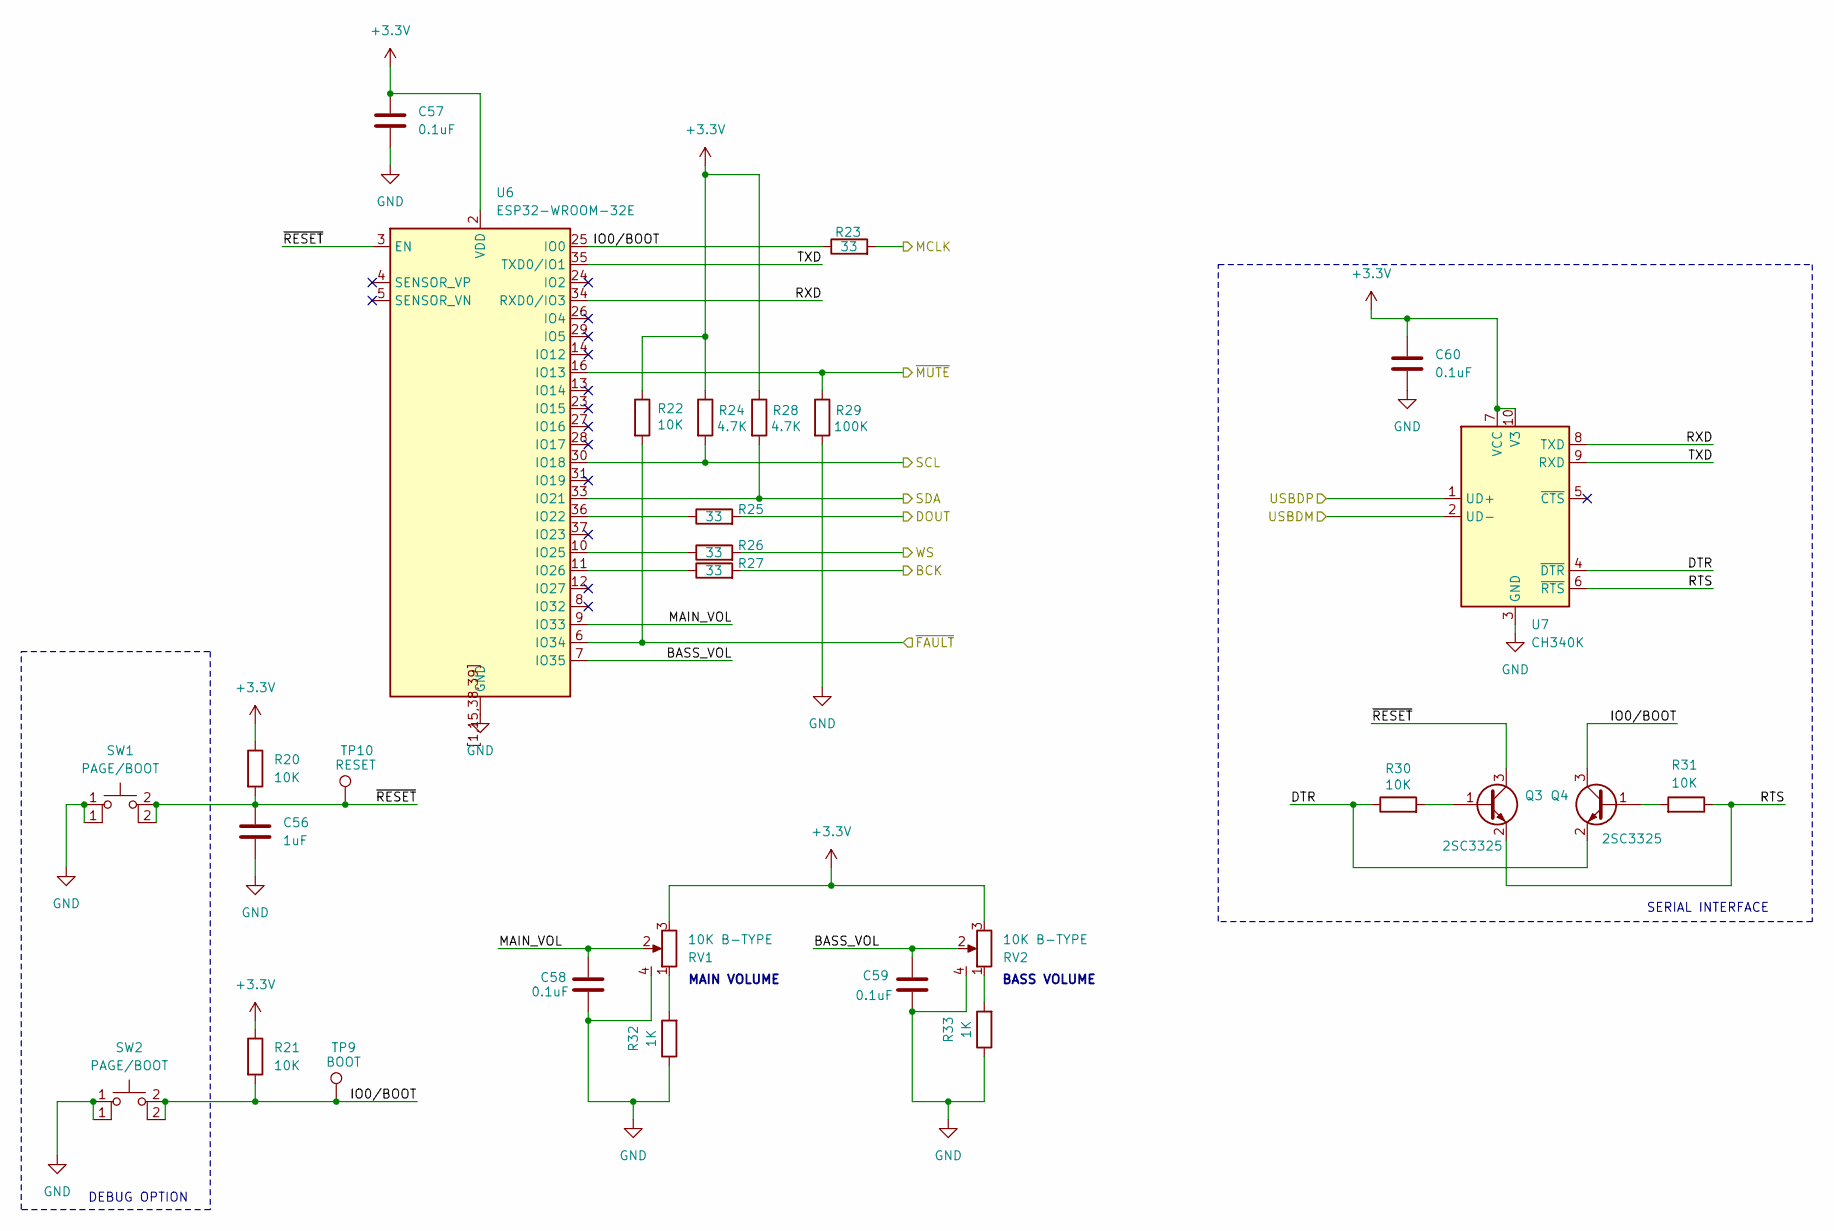
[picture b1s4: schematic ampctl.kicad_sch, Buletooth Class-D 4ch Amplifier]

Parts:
C56: 1uF; C_0805_2012Metric; digikey 1276-1026-1-ND
C57, C58, C59, C60: 0.1uF; C_0603_1608Metric; digikey 311-1343-1-ND
Q3, Q4: 2SC3325; SC-59; digikey 100628
R20, R21, R22, R30, R31: 10K; R_0603_1608Metric; digikey 311-10.0KHRCT-ND
R23, R25, R26, R27: 33; R_0603_1608Metric; digikey 13-RC0603JR-1333RCT-ND
R24, R28: 4.7K; R_0603_1608Metric; digikey 311-4.70KHRCT-ND
R29: 100K; R_0603_1608Metric; digikey 311-100KLDCT-ND
R32, R33: 1K; R_0603_1608Metric; digikey 311-1.00KHRCT-ND
RV1, RV2: 10K B-TYPE; Potentiometer_Alps_RK09L_Double_Horizontal; digikey 112576
SW1, SW2: PAGE/BOOT; SW_PUSH_6mm_H8mm; digikey 2223-TS02-66-70-BK-160-LCR-D-ND
TP9: BOOT; TestPoint_Pad_D1.0mm
TP10: RESET; TestPoint_Pad_D1.0mm
U6: ESP32-WROOM-32E; digikey 115675
U7: CH340K; SSOP-10-1EP_3.9x4.9mm_P1mm_EP2.1x3.3mm; digikey 116306

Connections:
+3.3V: C57.1, C60.1, R20.1, R21.1, R22.1, R24.1, R28.1, RV1.3, RV2.3, U6.2 (VDD), U7.7 (VCC), U7.10 (V3); also elsewhere on the board
/Amplifier Controller/BASS_VOL: C59.1, RV2.2, U6.7 (IO35)
/Amplifier Controller/BCK: R27.2; also elsewhere on the board
/Amplifier Controller/DOUT: R25.2; also elsewhere on the board
/Amplifier Controller/DTR: Q4.2 (E), R30.1, U7.4 (~DTR)
/Amplifier Controller/IO0/BOOT: Q4.3 (C), R21.2, R23.1, SW2.2, TP9.1 (1_1), U6.25 (IO0)
/Amplifier Controller/MAIN_VOL: C58.1, RV1.2, U6.9 (IO33)
/Amplifier Controller/MCLK: R23.2; also elsewhere on the board
/Amplifier Controller/RTS: Q3.2 (E), R31.1, U7.6 (~RTS)
/Amplifier Controller/RXD: U6.34 (RXD0/IO3), U7.8 (TXD)
/Amplifier Controller/SCL: R24.2, U6.30 (IO18); also elsewhere on the board
/Amplifier Controller/SDA: R28.2, U6.33 (IO21); also elsewhere on the board
/Amplifier Controller/TXD: U6.35 (TXD0/IO1), U7.9 (RXD)
/Amplifier Controller/USBDM: U7.2 (UD-); also elsewhere on the board
/Amplifier Controller/USBDP: U7.1 (UD+); also elsewhere on the board
/Amplifier Controller/WS: R26.2; also elsewhere on the board
/Amplifier Controller/~FAULT: R22.2, U6.6 (IO34); also elsewhere on the board
/Amplifier Controller/~MUTE: R29.1, U6.16 (IO13); also elsewhere on the board
/Amplifier Controller/~RESET: C56.1, Q3.3 (C), R20.2, SW1.2, TP10.1 (1_1), U6.3 (EN)
GND: C56.2, C57.2, C58.2, C59.2, C60.2, R29.2, R32.1, R33.1, RV1.4, RV2.4, SW1.1, SW2.1, U6.1 (GND), U6.15 (GND), U6.38 (GND), U6.39 (GND), U6.[1,15,38,39] (GND), U7.3 (GND), U7.11 (GND); also elsewhere on the board
unnamed: Q3.1 (B), R30.2
unnamed: Q4.1 (B), R31.2
unnamed: R32.2, RV1.1
unnamed: R33.2, RV2.1
unnamed: R25.1, U6.36 (IO22)
unnamed: R26.1, U6.10 (IO25)
unnamed: R27.1, U6.11 (IO26)

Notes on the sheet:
MAIN VOLUME
SERIAL INTERFACE
DEBUG OPTION
BASS VOLUME

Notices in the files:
hw/ampctl.kicad_sch:
Licensed under CC-BY-SA V4.0
hw/classDamp.kicad_pcb:
(C) 2026 HNZ DIGITAL SIGNAL PROCESSOR AND CLASS-D AMPLIFIER Rev1
